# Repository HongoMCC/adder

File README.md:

# adder

4bit full adder with 74HC00

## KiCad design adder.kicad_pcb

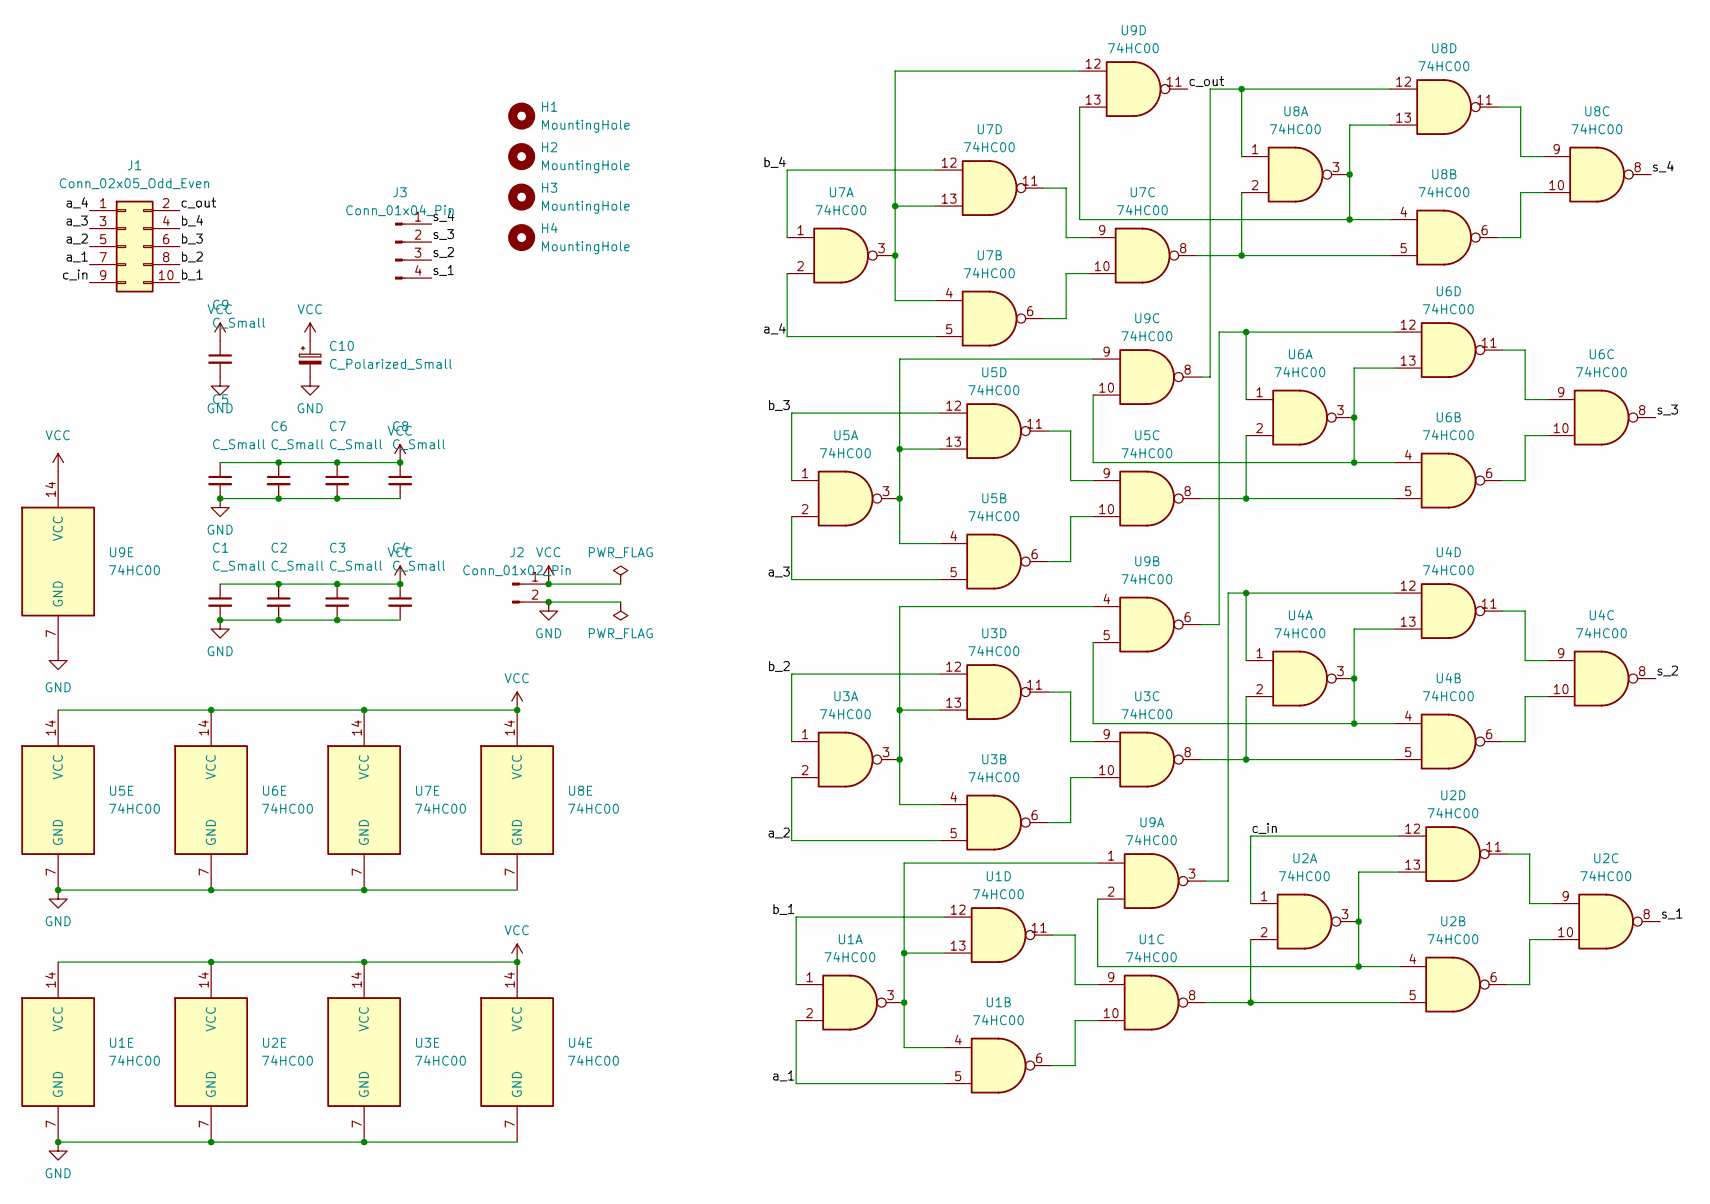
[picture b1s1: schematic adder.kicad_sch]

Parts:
C1, C2, C3, C4, C5, C6, C7, C8, C9: C_Small; C_Disc_D4.3mm_W1.9mm_P5.00mm
C10: C_Polarized_Small; CP_Radial_D5.0mm_P2.50mm
H1, H2, H3, H4: MountingHole; MountingHole_3.2mm_M3
J1: Conn_02x05_Odd_Even; PinHeader_2x05_P2.54mm_Vertical
J2: Conn_01x02_Pin; JST_XH_B2B-XH-A_1x02_P2.50mm_Vertical
J3: Conn_01x04_Pin; PinHeader_1x04_P2.54mm_Vertical
U1, U2, U3, U4, U5, U6, U7, U8, U9: 74HC00; DIP-14_W7.62mm_Socket

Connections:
/a_1: J1.7, U1.2, U1.5
/a_2: J1.5, U3.2, U3.5
/a_3: J1.3, U5.2, U5.5
/a_4: J1.1, U7.2, U7.5
/b_1: J1.10, U1.1, U1.12
/b_2: J1.8, U3.1, U3.12
/b_3: J1.6, U5.1, U5.12
/b_4: J1.4, U7.1, U7.12
/c_in: J1.9, U2.1, U2.12
/c_out: J1.2, U9.11
/s_1: J3.4, U2.8
/s_2: J3.3, U4.8
/s_3: J3.2, U6.8
/s_4: J3.1, U8.8
GND: C1.2, C2.2, C3.2, C4.2, C5.2, C6.2, C7.2, C8.2, C9.2, C10.2, J2.2, U1.7 (GND), U2.7 (GND), U3.7 (GND), U4.7 (GND), U5.7 (GND), U6.7 (GND), U7.7 (GND), U8.7 (GND), U9.7 (GND)
unnamed: U1.8, U2.2, U2.5
unnamed: U1.6, U1.10
unnamed: U1.9, U1.11
unnamed: U1.3, U1.4, U1.13, U9.1
unnamed: U2.6, U2.10
unnamed: U2.9, U2.11
unnamed: U2.3, U2.4, U2.13, U9.2
unnamed: U3.8, U4.2, U4.5
unnamed: U3.6, U3.10
unnamed: U3.9, U3.11
unnamed: U3.3, U3.4, U3.13, U9.4
unnamed: U4.1, U4.12, U9.3
unnamed: U4.6, U4.10
unnamed: U4.9, U4.11
unnamed: U4.3, U4.4, U4.13, U9.5
unnamed: U5.8, U6.2, U6.5
unnamed: U5.6, U5.10
unnamed: U5.9, U5.11
unnamed: U5.3, U5.4, U5.13, U9.9
unnamed: U6.1, U6.12, U9.6
unnamed: U6.6, U6.10
unnamed: U6.9, U6.11
unnamed: U6.3, U6.4, U6.13, U9.10
unnamed: U7.8, U8.2, U8.5
unnamed: U7.6, U7.10
unnamed: U7.9, U7.11
unnamed: U7.3, U7.4, U7.13, U9.12
unnamed: U8.1, U8.12, U9.8
unnamed: U8.6, U8.10
unnamed: U8.9, U8.11
unnamed: U8.3, U8.4, U8.13, U9.13
VCC: C1.1, C2.1, C3.1, C4.1, C5.1, C6.1, C7.1, C8.1, C9.1, C10.1, J2.1, U1.14 (VCC), U2.14 (VCC), U3.14 (VCC), U4.14 (VCC), U5.14 (VCC), U6.14 (VCC), U7.14 (VCC), U8.14 (VCC), U9.14 (VCC)

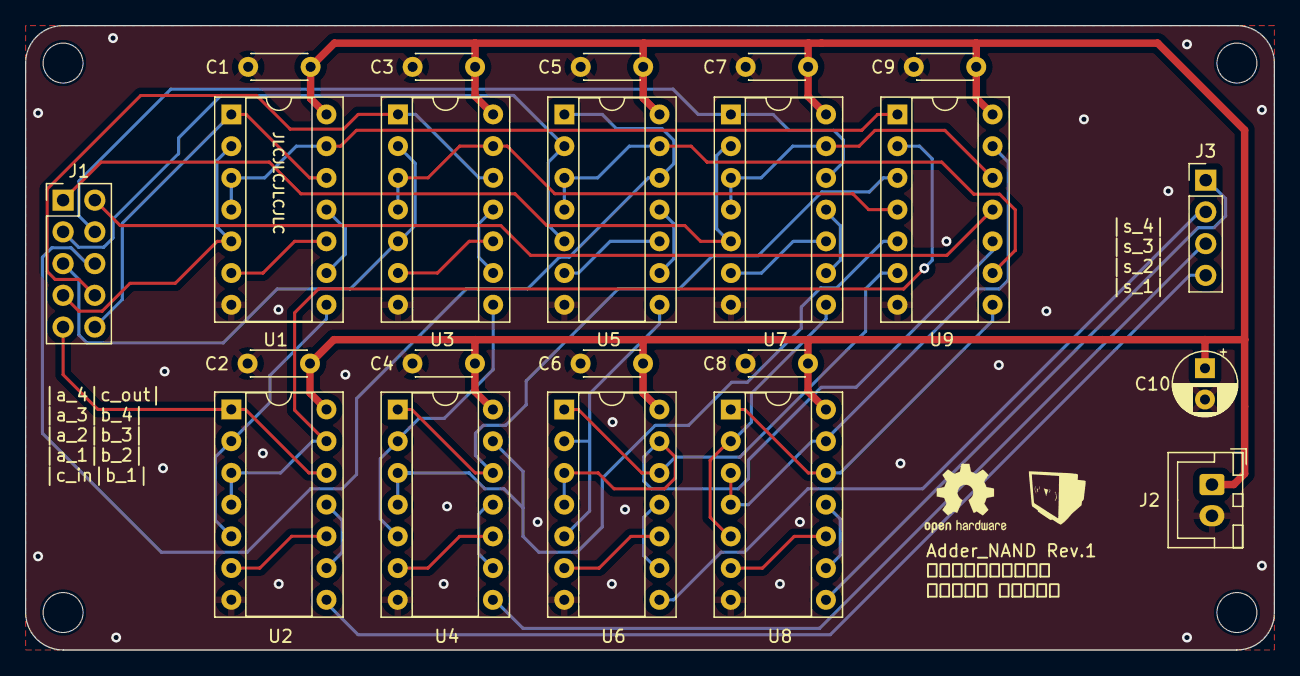
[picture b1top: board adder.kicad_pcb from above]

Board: 2 copper layers, 100.0 x 50.0 mm, 26 parts (0 on the bottom side), 47 nets.

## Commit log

2024-08-21 init
2024-08-21 up to date
2024-08-21 generate gerber files
2024-08-21 generate drill files
